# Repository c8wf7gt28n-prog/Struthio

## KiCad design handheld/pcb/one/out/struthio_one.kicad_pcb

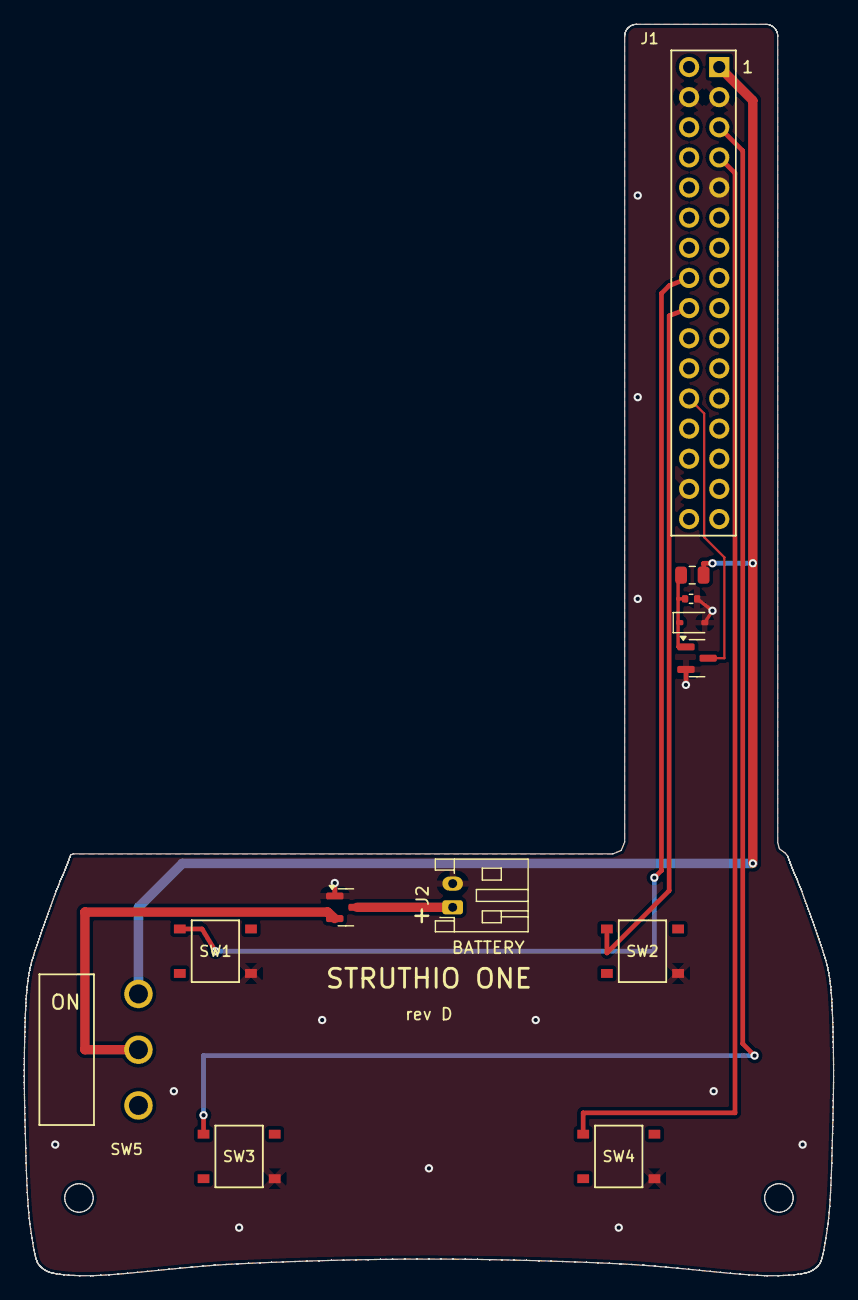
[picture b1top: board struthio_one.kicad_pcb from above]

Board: 2 copper layers, 68.2 x 105.5 mm, 12 parts (0 on the bottom side), 10 nets.

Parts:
C1: 10uF; C_0805_2012Metric
D1: 1N4148WS; D_SOD-323
J1: Header_2x16_Waveshare
J2: S2B-PH-K-S; JST_PH_S2B-PH-K_1x02_P2.00mm_Horizontal
Q1: AO3401A; SOT-23
Q2: AO3400A; SOT-23
R1: 470k; R_0402_1005Metric
SW1, SW2, SW3, SW4: TS-1187A-B-A-B
SW5: SS-12D06-G030

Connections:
BAT: C1.2, J1.1, SW5.1
BAT_IN: J2.1, Q1.3
BAT_RAW: Q1.2, SW5.2
GND: D1.2, J1.3, J1.4, J1.9, J1.29, J1.30, J2.2, Q1.1, Q2.2, R1.2, SW1.D, SW2.D, SW3.D, SW4.D
GPIO17: J1.16, SW1.A
GPIO18: J1.18, SW2.A
GPIO21: J1.5, SW3.A
GPIO38: J1.7, SW4.A
PG: C1.1, D1.1, Q2.1, R1.1
PWRON: J1.24, Q2.3

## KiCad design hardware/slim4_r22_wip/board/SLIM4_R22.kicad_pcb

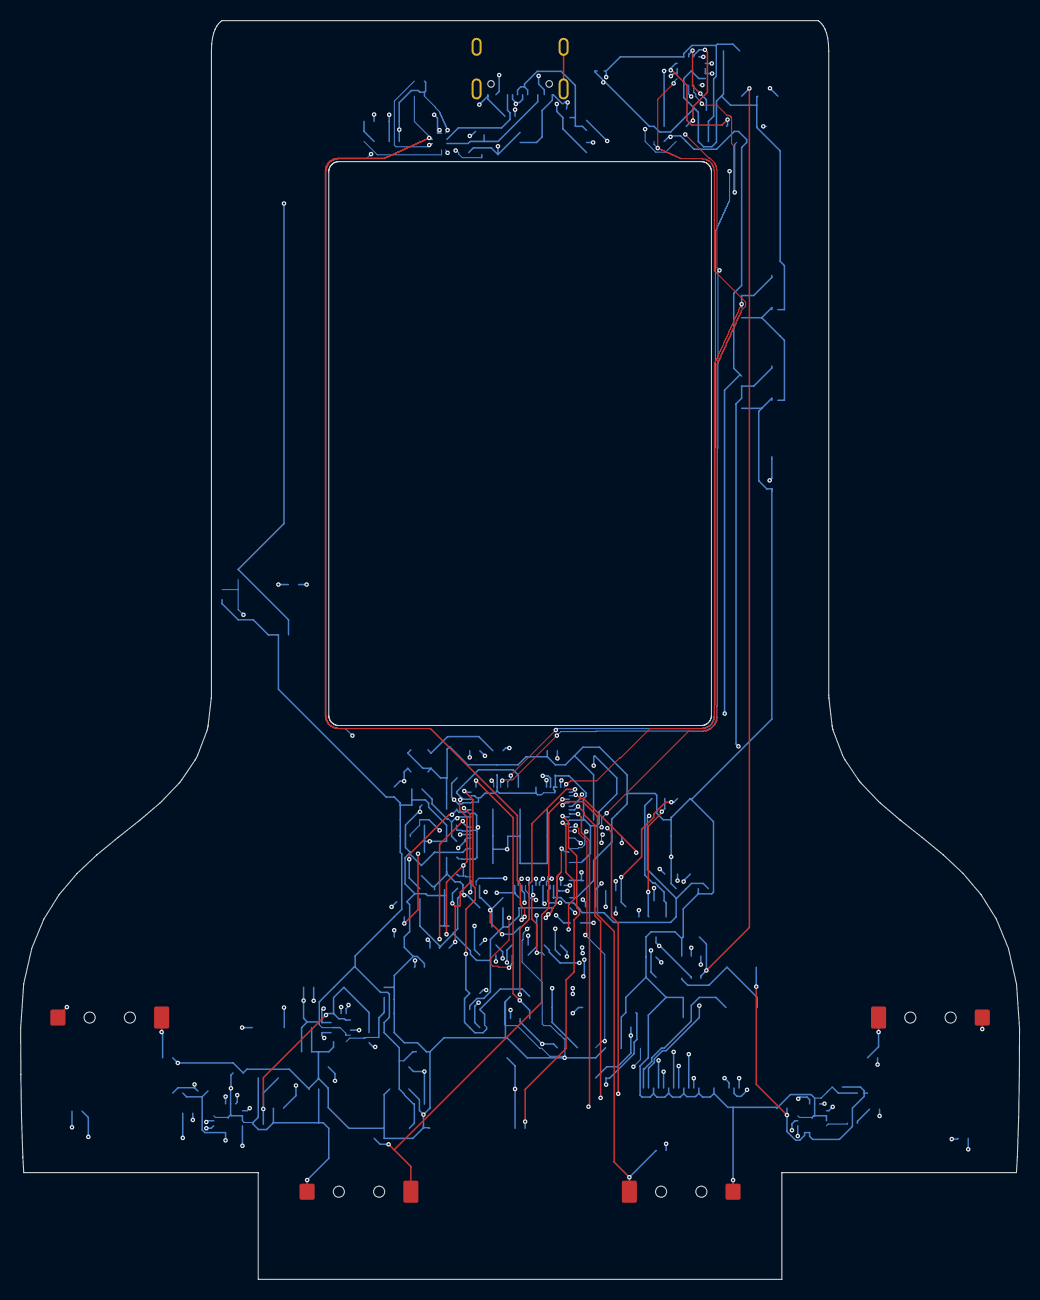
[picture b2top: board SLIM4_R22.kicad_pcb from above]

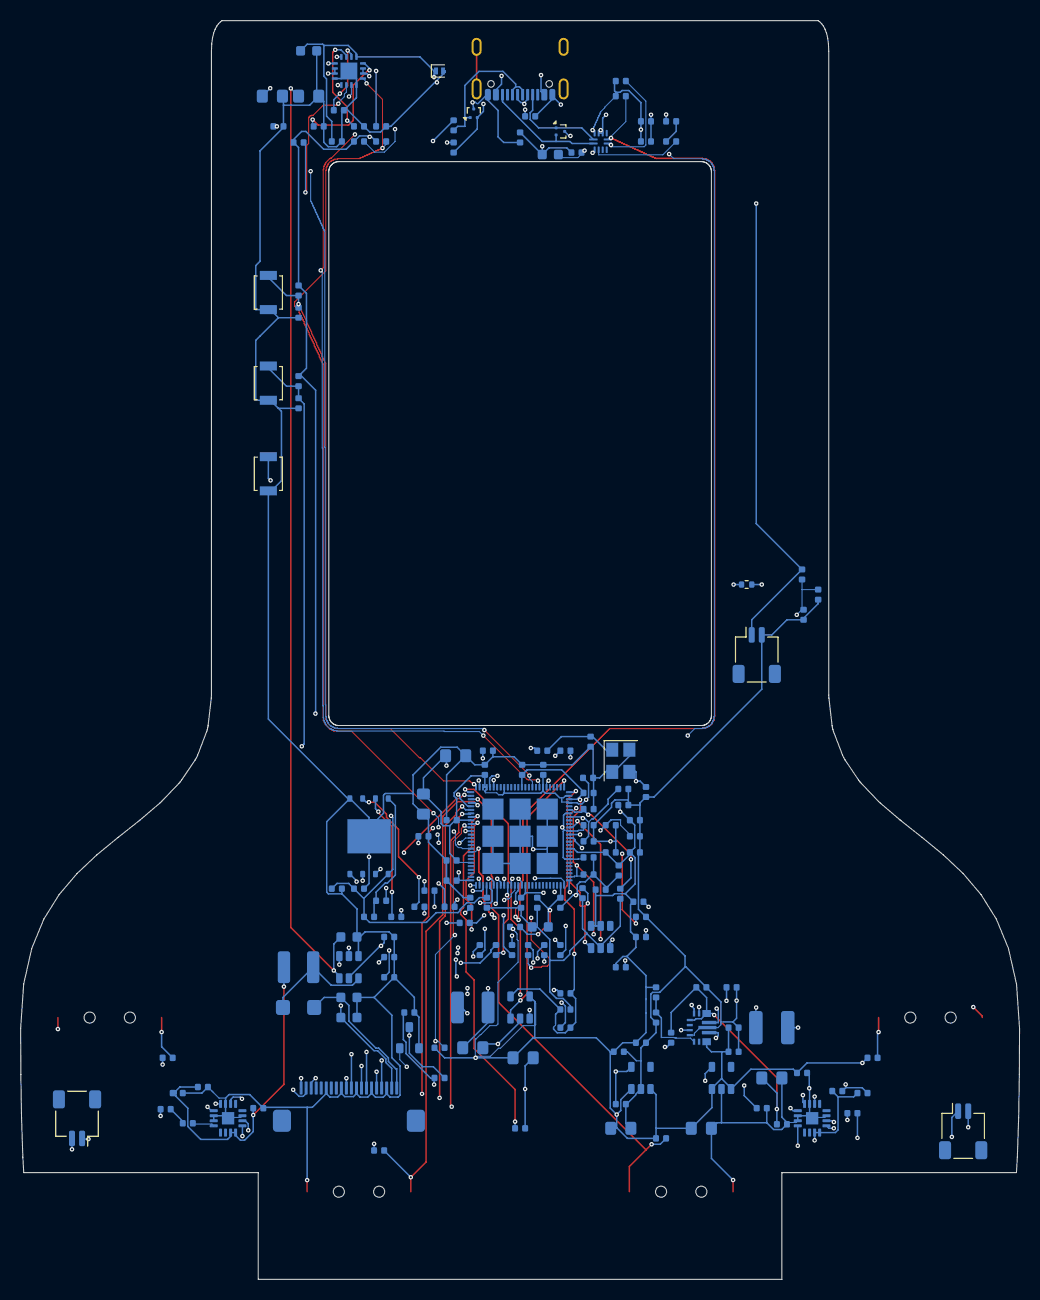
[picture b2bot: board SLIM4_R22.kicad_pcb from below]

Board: 6 copper layers, 99.2 x 125.0 mm, 166 parts (162 on the bottom side), 98 nets.

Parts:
C101: CL05B104KO5NNNC; FP_C101
C102: CL05B104KO5NNNC; FP_C102
C103: CL05B104KO5NNNC; FP_C103
C104: CL05B104KO5NNNC; FP_C104
C105: CL05B104KO5NNNC; FP_C105
C106: CL05B104KO5NNNC; FP_C106
C107: CL05B103KB5NNNC; FP_C107
C108: CL05B104KO5NNNC; FP_C108
C109: CL05A105KA5NQNC; FP_C109
C110: CL05B103KB5NNNC; FP_C110
C111: CL05B104KO5NNNC; FP_C111
C112: CL10A475KO8NNNC; FP_C112
C113: CL05B104KO5NNNC; FP_C113
C114: CL05B104KO5NNNC; FP_C114
C115: CL05A105KA5NQNC; FP_C115
C116: CL05B104KO5NNNC; FP_C116
C117: CL05B104KO5NNNC; FP_C117
C118: CL05A105KA5NQNC; FP_C118
C119: CL05A105KA5NQNC; FP_C119
C120: CL05A105KA5NQNC; FP_C120
C121: CL05A105KA5NQNC; FP_C121
C122: CL05A105KA5NQNC; FP_C122
C123: CL21A106KAYNNNE; FP_C123
C124: CL05B104KO5NNNC; FP_C124
C125: CL05B104KO5NNNC; FP_C125
C126: CL21A106KAYNNNE; FP_C126
C127: CL05B104KO5NNNC; FP_C127
C128: CL05B104KO5NNNC; FP_C128
C129: CL05B104KO5NNNC; FP_C129
C130: CL05B104KO5NNNC; FP_C130
C131: CL05B104KO5NNNC; FP_C131
C132: CL05B104KO5NNNC; FP_C132
C133: CL21A106KAYNNNE; FP_C133
C134: 0402 C0G 22pF; FP_C134
C135: CL21A226MQQNNNE; FP_C135
C136: CL05A105KA5NQNC; FP_C136
C201: CL05B104KO5NNNC; FP_C201
C202: CL05A105KA5NQNC; FP_C202
C203: 0402CG120J500NT; FP_C203
C204: 0402CG120J500NT; FP_C204
C301: CL05B104KO5NNNC; FP_C301
C302: CL05B104KO5NNNC; FP_C302
C303: CL05B104KO5NNNC; FP_C303
C304: CL05B104KO5NNNC; FP_C304
C305: CL05A105KA5NQNC; FP_C305
C306: CL05A105KA5NQNC; FP_C306
C307: CL05A105KA5NQNC; FP_C307
C308: CL05A105KA5NQNC; FP_C308
C309: CL10A105KB8NNNC; FP_C309
C310: CL05B224KO5NNNC; FP_C310
C311: CL10A475KO8NNNC; FP_C311
C401: CL05B104KO5NNNC; FP_C401
C402: CL05B104KO5NNNC; FP_C402
C403: CL05B104KO5NNNC; FP_C403
C404: CL05B104KO5NNNC; FP_C404
C405: CL05B104KO5NNNC; FP_C405
C406: CL05B104KO5NNNC; FP_C406
C407: CL05B104KO5NNNC; FP_C407
C408: CL05A105KA5NQNC; FP_C408
C409: CL10A475KO8NNNC; FP_C409
C410: CL10A475KO8NNNC; FP_C410
C411: CL21A106KAYNNNE; FP_C411
C412: CL21A106KAYNNNE; FP_C412
C413: CL21A226MQQNNNE; FP_C413
C414: CL21A226MQQNNNE; FP_C414
C415: CL21A226MQQNNNE; FP_C415
C501: CL05B104KO5NNNC; FP_C501
C502: CL05B104KO5NNNC; FP_C502
C503: CL05B104KO5NNNC; FP_C503
C504: CL05B104KO5NNNC; FP_C504
C505: CL05A105KA5NQNC; FP_C505
C506: CL05A105KA5NQNC; FP_C506
C601: CL05B104KO5NNNC; FP_C601
C602: CL05B104KO5NNNC; FP_C602
C603: CL05B104KO5NNNC; FP_C603
D1: PESD5V0S1UL,315; FP_D1
D2: STPS1L40ZFY; FP_D2
J1: FH12-20S-0.5SH(55); FP_J1
J2: USB4105-GF-A-120; FP_J2
J3: SM02B-SRSS-TB(LF)(SN); FP_J3
J4: SM02B-SRSS-TB(LF)(SN); FP_J4
J5: SM02B-SRSS-TB(LF)(SN); FP_J5
L1: MWSA0402S-1R0MT; FP_L1
L2: ASWPA4035S2R2MT; FP_L2
L3: WPN4020H100MT; FP_L3
Q1: 2N7002; FP_Q1
R103: 0402WGF4021TCE; FP_R103
R104: 0402WGF4993TCE; FP_R104
R105: 0402WGF4993TCE; FP_R105
R106: 0402WGF1002TCE; FP_R106
R107: 0402WGF1002TCE; FP_R107
R108: 0402WGF1002TCE; FP_R108
R109: 0402WGF1002TCE; FP_R109
R110: 0402WGF1002TCE; FP_R110
R111: 0402WGF1002TCE; FP_R111
R112: 0402WGF1002TCE; FP_R112
R201: 0402WGF0000TCE; FP_R201
R202: 0402WGF0000TCE; FP_R202
R203: 0402WGF0000TCE; FP_R203
R204: 0402WGF0000TCE; FP_R204
R205: 0402WGF0000TCE; FP_R205
R206: 0402WGF0000TCE; FP_R206
R207: 0402WGF0000TCE; FP_R207
R208: 0402WGF0000TCE; FP_R208
R209: 0402WGF1002TCE; FP_R209
R301: 0402WGF0000TCE; FP_R301
R302: 0402WGF0000TCE; FP_R302
R303: 0402WGF0000TCE; FP_R303
R304: 0402WGF0000TCE; FP_R304
R305: 0402WGF0000TCE; FP_R305
R306: 0402WGF0000TCE; FP_R306
R307: 0402WGF1002TCE; FP_R307
R308: 0402WGF1003TCE; FP_R308
R309: 0603WAF510KT5E; FP_R309
R401: 0402WGF0000TCE; FP_R401
R402: 0402WGF0000TCE; FP_R402
R403: 0402WGF0000TCE; FP_R403
R404: 0402WGF0000TCE; FP_R404
R410: 0402WGF4703TCE; FP_R410
R411: 0402WGF1503TCE; FP_R411
R412: 0402WGF3601TCE; FP_R412
R413: 0402WGF3301TCE; FP_R413
R414: 0402WGF4702TCE; FP_R414
R415: 0402WGF1501TCE; FP_R415
R416: 0402WGF4703TCE; FP_R416
R417: 0402WGF4303TCE; FP_R417
R418: 0402WGF1003TCE; FP_R418
R419: 0402WGF3302TCE; FP_R419
R420: 0402WGF1003TCE; FP_R420
R421: 0402WGF1003TCE; FP_R421
R422: 0402WGF1003TCE; FP_R422
R423: 0402WGF1003TCE; FP_R423
R424: 0402WGF1002TCE; FP_R424
R501: 0402WGF2001TCE; FP_R501
R502: 0402WGF1003TCE; FP_R502
R503: 0402WGF1103TCE; FP_R503
R504: 0402WGF1003TCE; FP_R504
R601: 0402WGF1002TCE; FP_R601
R602: 0402WGF1002TCE; FP_R602
R603: 0402WGF1002TCE; FP_R603
R604: 0402WGF1002TCE; FP_R604
R605: 0402WGF1002TCE; FP_R605
R606: 0402WGF1002TCE; FP_R606
R607: 0402WGF1002TCE; FP_R607
SW1: D2LS-21; FP_SW1
SW2: D2LS-21; FP_SW2
SW3: D2LS-21; FP_SW3
SW4: D2LS-21; FP_SW4
SW5: B3U-1000P; FP_SW5
SW6: B3U-1000P; FP_SW6
SW7: B3U-1000P; FP_SW7
U1: ESP32-P4NRW32X; FP_U1
U2: W25Q512JVEIQ TR; FP_U2
U3: TLV62569DBVR; FP_U3
U4: TPS63070RNMR; FP_U4
U5: TLV75518PDBVR; FP_U5
U6: ME6211C30M5G-N; FP_U6
U7: TPS61165DBVR; FP_U7
U8: MAX98357AETE+T; FP_U8
U9: MAX98357AETE+T; FP_U9
U10: BQ24074RGTR; FP_U10
U11: TPD2EUSB30DRTR; FP_U11
U12: TPD2EUSB30DRTR; FP_U12
U13: TUSB320LAIRWBR; FP_U13
U14: TPS3808G33DBVR; FP_U14
Y1: L327S400H11L; FP_Y1

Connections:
1V1_HP: C103.1, C105.1, C125.1, C129.1, C134.1, C135.1, L2.2, R104.1, U1.26, U1.54, U1.76, U1.91
3V3_ENABLE: R423.2, U4.14
3V3_SYS: C101.1, C102.1, C106.1, C114.1, C117.1, C123.1, C124.1, C126.1, C127.1, C128.1, C130.1, C131.1, C132.1, C133.1, C302.1, C303.1, C305.1, C307.1, C404.1, C405.1, C406.1, C407.1, C408.1, C410.1, C414.1, C415.1, R106.1, R108.1, R109.1, R110.1, R111.1, R112.1, R308.1, R403.1, R410.1, R420.1, R421.1, R601.1, R602.1, R603.1, R605.1, R606.1, R607.1, U1.9, U1.21, U1.62, U1.75, U1.77, U1.85, U1.96, U1.101, U1.102, U3.4, U4.7, U4.8, U5.1, U5.3, U6.1, U6.3, U13.12, U14.5, U14.6
AUDIO_SD_CTRL: R501.1, R502.1, R504.1, U1.8
AUDIO_SD_L: R501.2, U8.4
AUDIO_SD_R: R503.2, U9.4
AUDIO_SD_R_MID: R502.2, R503.1
BACKLIGHT_PWM: R422.1, U1.10, U7.2
BAT_ADC: C603.1, R418.2, R419.1, U1.17
BAT_PLUS: C412.1, J3.1, R418.1, U10.2, U10.3
BL_COMP: C310.1, U7.5
BL_SW: D2.A, L3.2, U7.3
BOOT_STRAP: R108.2, SW7.1, U1.66
BQ_EN1: R603.2, U1.14, U10.6
BQ_EN2: R604.1, U1.88, U10.5
BQ_ILIM: R415.1, U10.12
BQ_ISET: R412.1, U10.16
BQ_ITERM: R413.1, U10.15
BQ_TMR: R414.1, U10.14
BQ_TS: R424.1, U10.1
BTN_LEFT: R111.2, SW1.COM, U1.1
BTN_RIGHT: R112.2, SW2.COM, U1.2
CHASSIS_GND: J2.SH, R404.1
CHG_STATUS: R420.2, U1.12, U10.9
CHIP_PU: C136.1, R106.2, U1.103, U14.1
CORE_SW: L2.1, U3.3
DART_LEFT: R601.2, SW3.COM, U1.3
DART_RIGHT: R602.2, SW4.COM, U1.4
DOWNLOAD_STRAP_GPIO36: R109.2, U1.68
DSI_CLK_N_SOC: R302.1, U1.37
DSI_CLK_P_SOC: R301.1, U1.38
DSI_D0_N_SOC: R304.1, U1.40
DSI_D0_P_SOC: R303.1, U1.39
DSI_D1_N_SOC: R306.1, U1.36
DSI_D1_P_SOC: R305.1, U1.35
DSI_REXT: R103.1, U1.34
EN_DCDC: U1.79, U3.1
FB_DCDC: C134.2, R104.2, R105.1, U1.78, U3.5
FLASH_CLK: R202.2, U2.6
FLASH_CLK_SOC: R202.1, U1.32
FLASH_CS_N: R201.2, R209.2, U2.1
FLASH_CS_SOC: R201.1, U1.27
FLASH_IO0: R203.2, U2.5
FLASH_IO0_SOC: R203.1, U1.33
FLASH_IO1: R204.2, U2.2
FLASH_IO1_SOC: R204.1, U1.28
FLASH_IO2: R205.2, U2.3
FLASH_IO2_SOC: R205.1, U1.29
FLASH_IO3: R206.2, U2.7
FLASH_IO3_SOC: R206.1, U1.31
GND: C101.2, C102.2, C103.2, C104.2, C105.2, C106.2, C107.2, C108.2, C109.2, C110.2, C111.2, C112.2, C113.2, C114.2, C115.2, C116.2, C117.2, C118.2, C119.2, C120.2, C121.2, C122.2, C123.2, C124.2, C125.2, C126.2, C127.2, C128.2, C129.2, C130.2, C131.2, C132.2, C133.2, C135.2, C136.2, C201.2, C202.2, C203.2, C204.2, C301.2, C302.2, C303.2, C304.2, C305.2, C306.2, C307.2, C308.2, C309.2, C310.2, C311.2, C401.2, C402.2, C403.2, C404.2, C405.2, C406.2, C407.2, C408.2, C409.2, C410.2, C411.2, C412.2, C413.2, C414.2, C415.2, C501.2, C502.2, C503.2, C504.2, C505.2, C506.2, C601.2, C602.2, C603.2, D1.2, J1.6, J1.9, J1.12, J1.15, J1.18, J2.A1, J2.A12, J2.B1, J2.B12, J3.2, Q1.2, R103.2, R105.2, R107.2, R309.2, R404.2, R411.2, R412.2, R413.2, R414.2, R415.2, R419.2, R422.2, R424.2, R504.2, R604.2, SW1.NO, SW2.NO, SW3.NO, SW4.NO, SW5.2, SW6.2, SW7.2, U1.105, U2.4, U2.EP, U3.2, U4.4, U4.10, U4.15, U5.2, U6.2, U7.4, U8.2, U8.3, U8.11, U8.15, U8.EP, U9.2, U9.3, U9.11, U9.15, U9.EP, U10.4, U10.8, U10.EP, U11.3, U12.3, U13.3, U13.10, U13.11, U14.2, Y1.2, Y1.4
I2S_BCLK: U1.5, U8.16, U9.16
I2S_DOUT: U1.7, U8.1, U9.1
I2S_LRCLK: U1.6, U8.14, U9.14
LCD_1V8: C304.1, C306.1, J1.3, R307.1, U5.5
LCD_LED_A: C309.1, D2.K, J1.20
LCD_LED_K: J1.19, R309.1, U7.6
LCD_RESET_GATE: Q1.1, R308.2, U1.11
LCD_RESX: J1.1, Q1.3, R307.2
LCD_VCI_3V0: C308.1, J1.2, U6.5
MIPI_DSI_CLK_N: J1.11, R302.2
MIPI_DSI_CLK_P: J1.10, R301.2
MIPI_DSI_D0_N: J1.17, R304.2
MIPI_DSI_D0_P: J1.16, R303.2
MIPI_DSI_D1_N: J1.14, R306.2
MIPI_DSI_D1_P: J1.13, R305.2
PGOOD_STATUS: R421.2, U1.86, U10.7
PWR_WAKE: C601.1, R110.2, SW5.1, U1.104
RESET_MR: C602.1, R607.2, SW6.1, U14.3
SPK_L_N: J4.2, U8.10
SPK_L_P: J4.1, U8.9
SPK_R_N: J5.2, U9.10
SPK_R_P: J5.1, U9.9
STRAP_GPIO34: R107.1, U1.65
SYS_RAW: C301.1, C311.1, C402.1, C411.1, C413.1, C501.1, C502.1, C503.1, C504.1, C505.1, C506.1, L3.1, R423.1, U4.1, U4.12, U4.13, U7.1, U8.7, U8.8, U9.7, U9.8, U10.10, U10.11
U4_FB: R410.2, R411.1, U4.5
U4_L1_SW: L1.1, U4.11
U4_L2_SW: L1.2, U4.9
U4_VAUX: C401.1, U4.3
USB_CC1: J2.A5, U12.1, U13.1
USB_CC2: J2.B5, U12.2, U13.2
USB_CURR_OUT1: R605.2, U1.84, U13.7
USB_CURR_OUT2: R606.2, U1.18, U13.8
USB_DM_CONN: J2.A7, J2.B7, R402.2, U11.2
USB_DP_CONN: J2.A6, J2.B6, R401.2, U11.1
USB_JTAG_DM: R402.1, U1.52
USB_JTAG_DP: R401.1, U1.53
USB_VBUS: C403.1, C409.1, D1.1, J2.A4, J2.A9, J2.B4, J2.B9, R416.1, U10.13
USB_VBUS_SENSE: R417.2, U13.4
USB_VBUS_SENSE_MID: R416.2, R417.1
VDDO_FLASH_3V3: C104.1, C115.1, C120.1, C201.1, C202.1, R209.1, U1.30, U1.71, U2.8
VDDO_MIPI_2V5: C107.1, C108.1, C109.1, C122.1, U1.41, U1.73
VDDO_PSRAM_1V9: C113.1, C116.1, C118.1, C119.1, C121.1, U1.59, U1.67, U1.72
VDD_USBPHY_LOCAL: C110.1, C111.1, C112.1, R403.2, U1.51
XTAL_N: C204.1, R208.2, Y1.3
XTAL_N_SOC: R208.1, U1.99
XTAL_P: C203.1, R207.2, Y1.1
XTAL_P_SOC: R207.1, U1.100
